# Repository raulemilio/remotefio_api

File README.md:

# BBRemoteIO - BeagleBone Black Remote I/O System

BBRemoteIO es un sistema de adquisición y control remoto basado en BeagleBone Black, diseñado para gestionar entradas y salidas de hardware a través de mensajes MQTT. Este módulo electrónico permite la integración con sensores, actuadores y otros dispositivos mediante la lectura de ADC, control de GPIOs y manejo de motores. Además, soporta la ejecución en paralelo de múltiples tareas y la integración con la PRU para adquisición de datos de alta velocidad. Ideal para aplicaciones en automatización, monitoreo remoto y laboratorios de instrumentación.

## Overview

BBRemoteIO is a remote I/O system for the BeagleBone Black, designed to execute tasks based on MQTT messages. The system can handle multiple tasks in parallel, including ADC data acquisition, GPIO input/output control, motor control, and interaction with an LCD display.

## Features

- **ADC Sampling**: Supports continuous sampling and triggered sampling.
- **GPIO Input/Output**: Reads input states and sets output states.
- **Motor Control**: Enables setting and querying motor states.
- **PRU Integration**: Uses the PRU for high-speed ADC data acquisition.
- **LCD Display**: Future module for logging and status display.
- **Parallel Execution**: Designed to handle multiple MQTT tasks without blocking.

## PRU (Cap15.pagina 667 libro BB)

### The PRU Code Generation Tools:

Download the PRU development framework from:
[PRU-CGT Tool](https://www.ti.com/tool/download/PRU-CGT)

Follow the project construction methodology as per the template: [Template Link](https://old.beagleboard.org/static/librobotcontrol/project_template.html)

## Compiling and Running ONLY PRU0

2. Configure GPIO pins:
   ```bash
   config-pin P8_16 pruin
   ```
   For more configuration options:
   ```bash
   config-pin -l P9_11
   ```
   To see the current configuration:
   ```bash
   config-pin -q P9_11
   ```

3. To export the pin and configure it:
```bash
echo "30" > /sys/class/gpio/export
echo "out" > /sys/class/gpio/gpio30/direction
echo "1" > /sys/class/gpio/gpio30/value  # Set high
echo "0" > /sys/class/gpio/gpio30/value  # Set low
```

4. Compile and load PRU firmware.

5. Check PRU state:
```bash
$ echo 'start' > /sys/class/remoteproc/remoteproc1/state
$ echo 'stop' > /sys/class/remoteproc/remoteproc1/state
```

### View PRU Registers:
```bash
$ sudo cat /sys/kernel/debug/remoteproc/remoteproc1/regs
```

### Test MQTT locally:

In one terminal:
```bash
$ mosquitto_sub -h localhost -t "test/topic"
```

In another terminal:
```bash
$ mosquitto_pub -h localhost -t "test/topic" -m "¡Hola desde BeagleBone!"
```

### Test MQTT between BeagleBone and Server:

1. Ping the server:
```bash
$ ping 192.168.0.171
```

2. On the notebook, open MQTT Explorer and connect to `tcp://192.168.0.171:1883`.
3. Subscribe to `test/topic` and send a message.

### Test MQTT Project:

Run the test MQTT project:
```bash
$ ./test_mqtt
```

## ADC Circuit

Based on:
- Book: "Analog Engineer's Circuit" (2023) Pg. 163
- Book: "Analog Engineer's Circuit" (2024) Pg. 160
- BeagleBook-Tool Pg. 443 (445 has protection for ADC inputs)
- Pg. 290 GIO

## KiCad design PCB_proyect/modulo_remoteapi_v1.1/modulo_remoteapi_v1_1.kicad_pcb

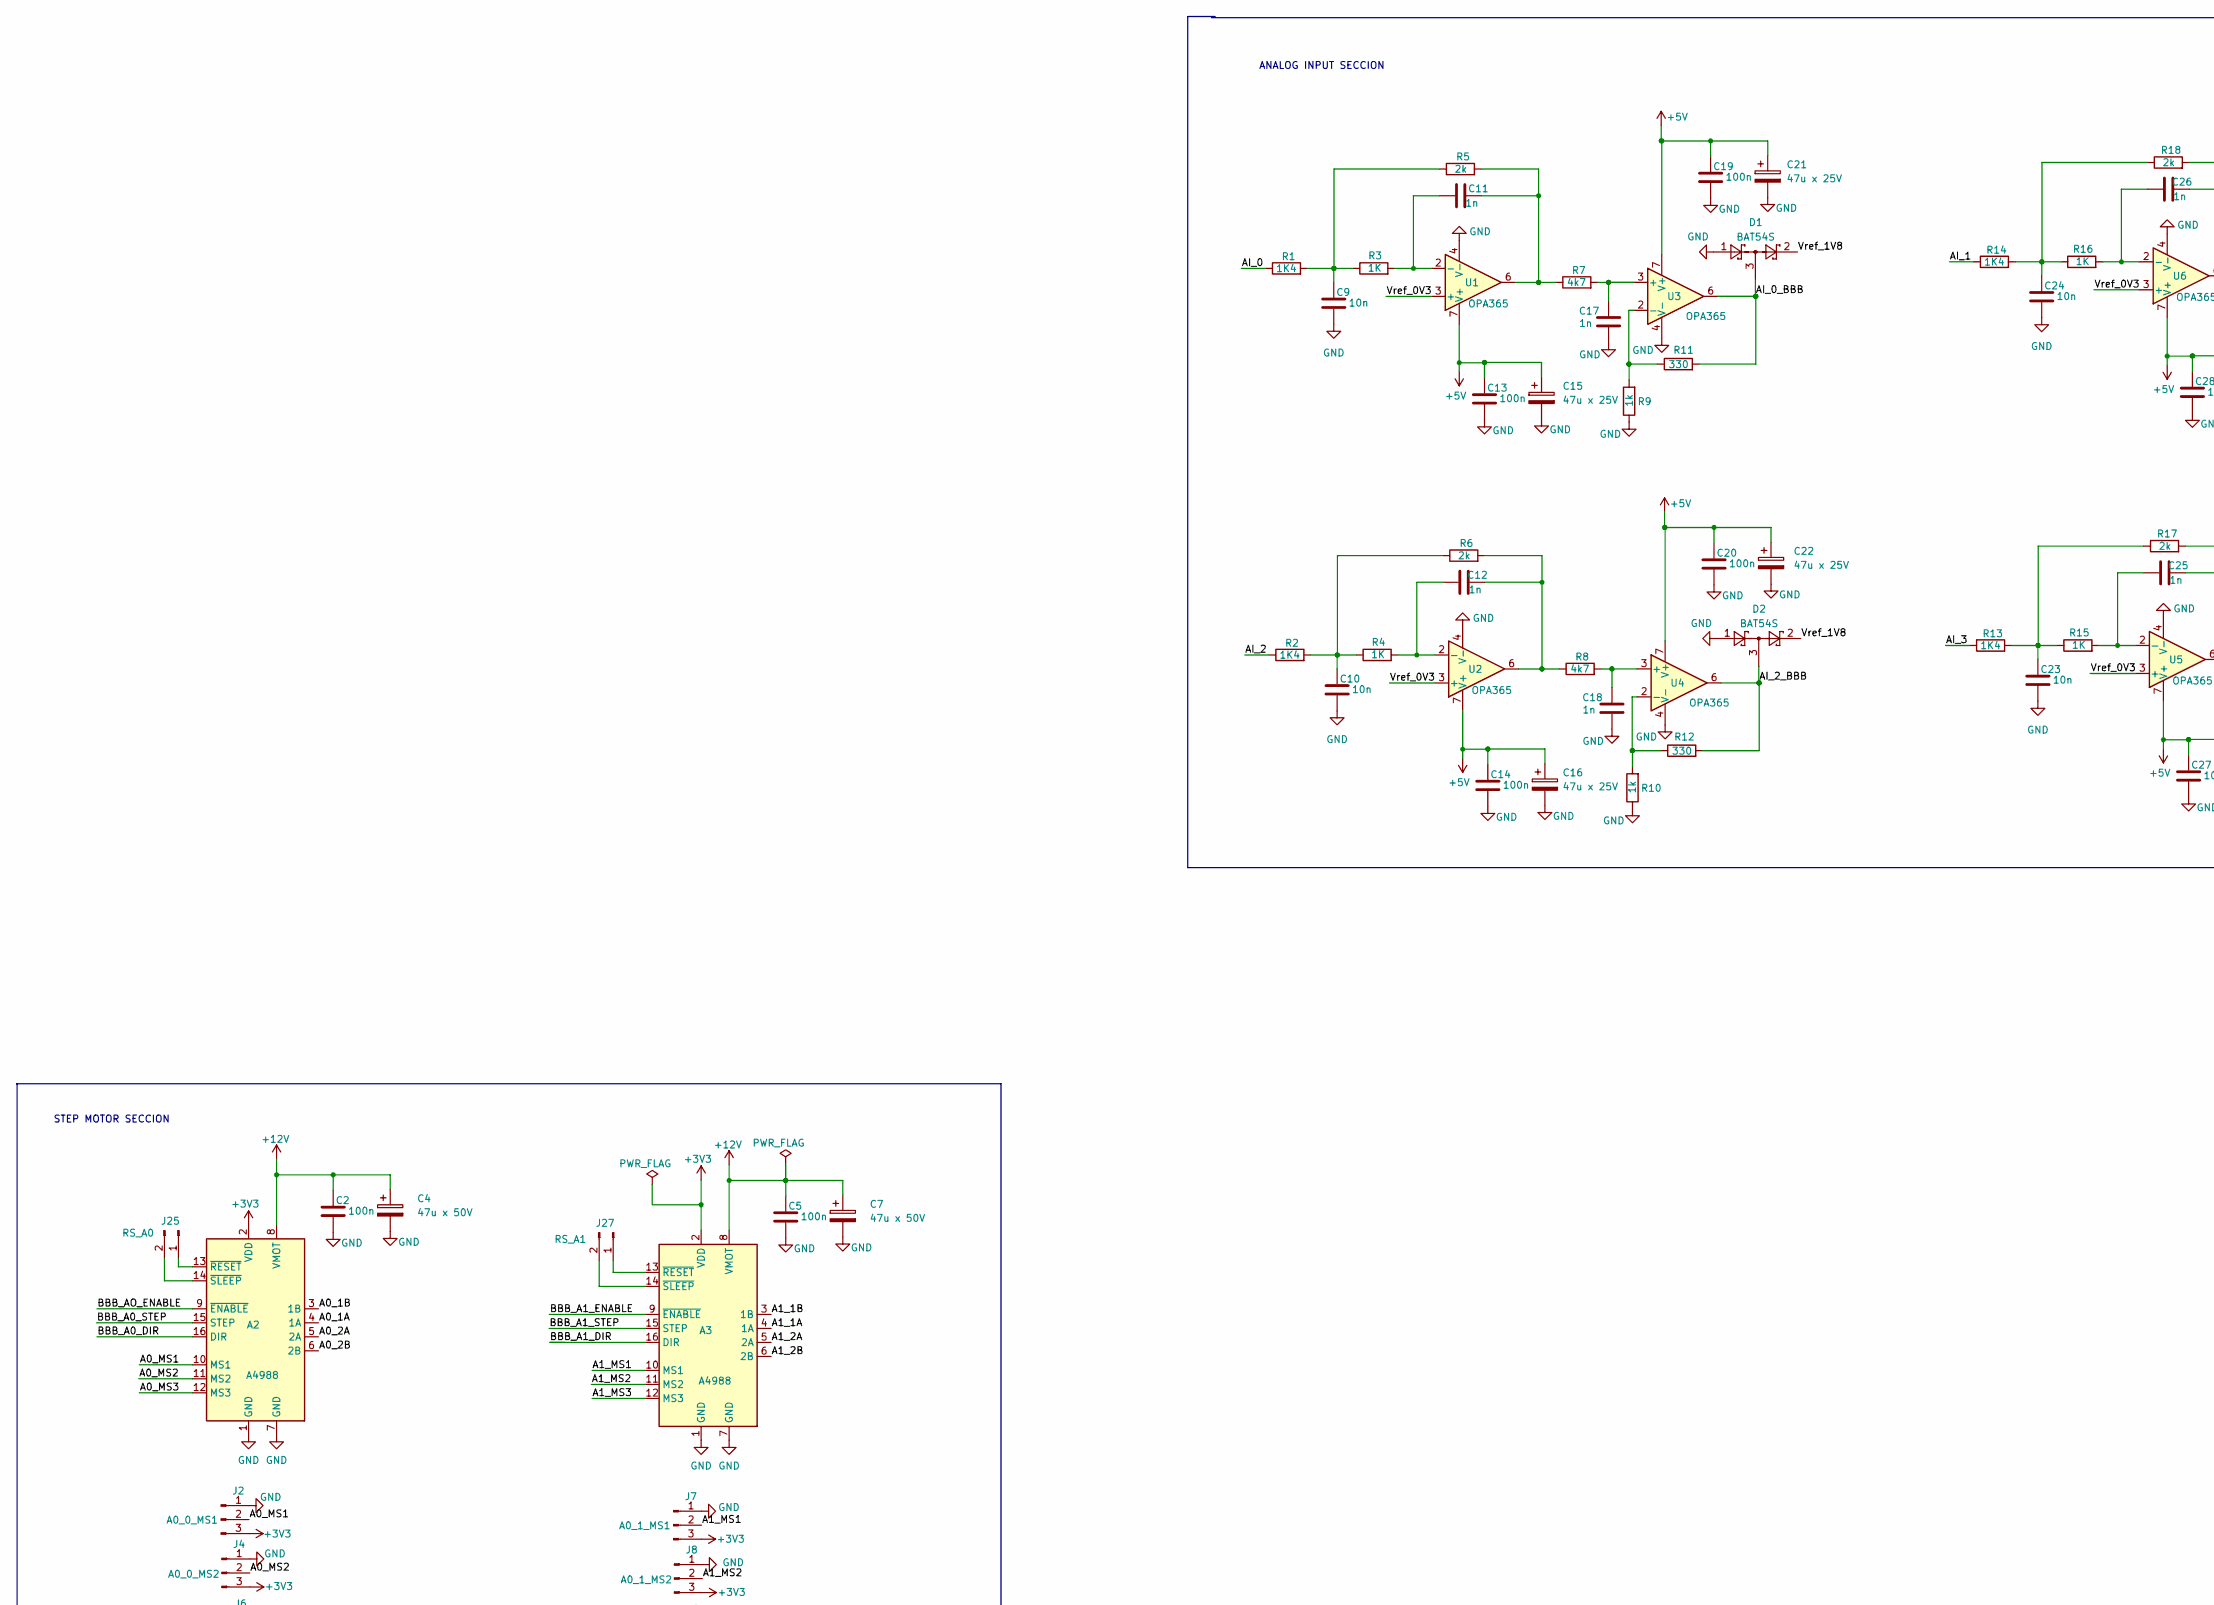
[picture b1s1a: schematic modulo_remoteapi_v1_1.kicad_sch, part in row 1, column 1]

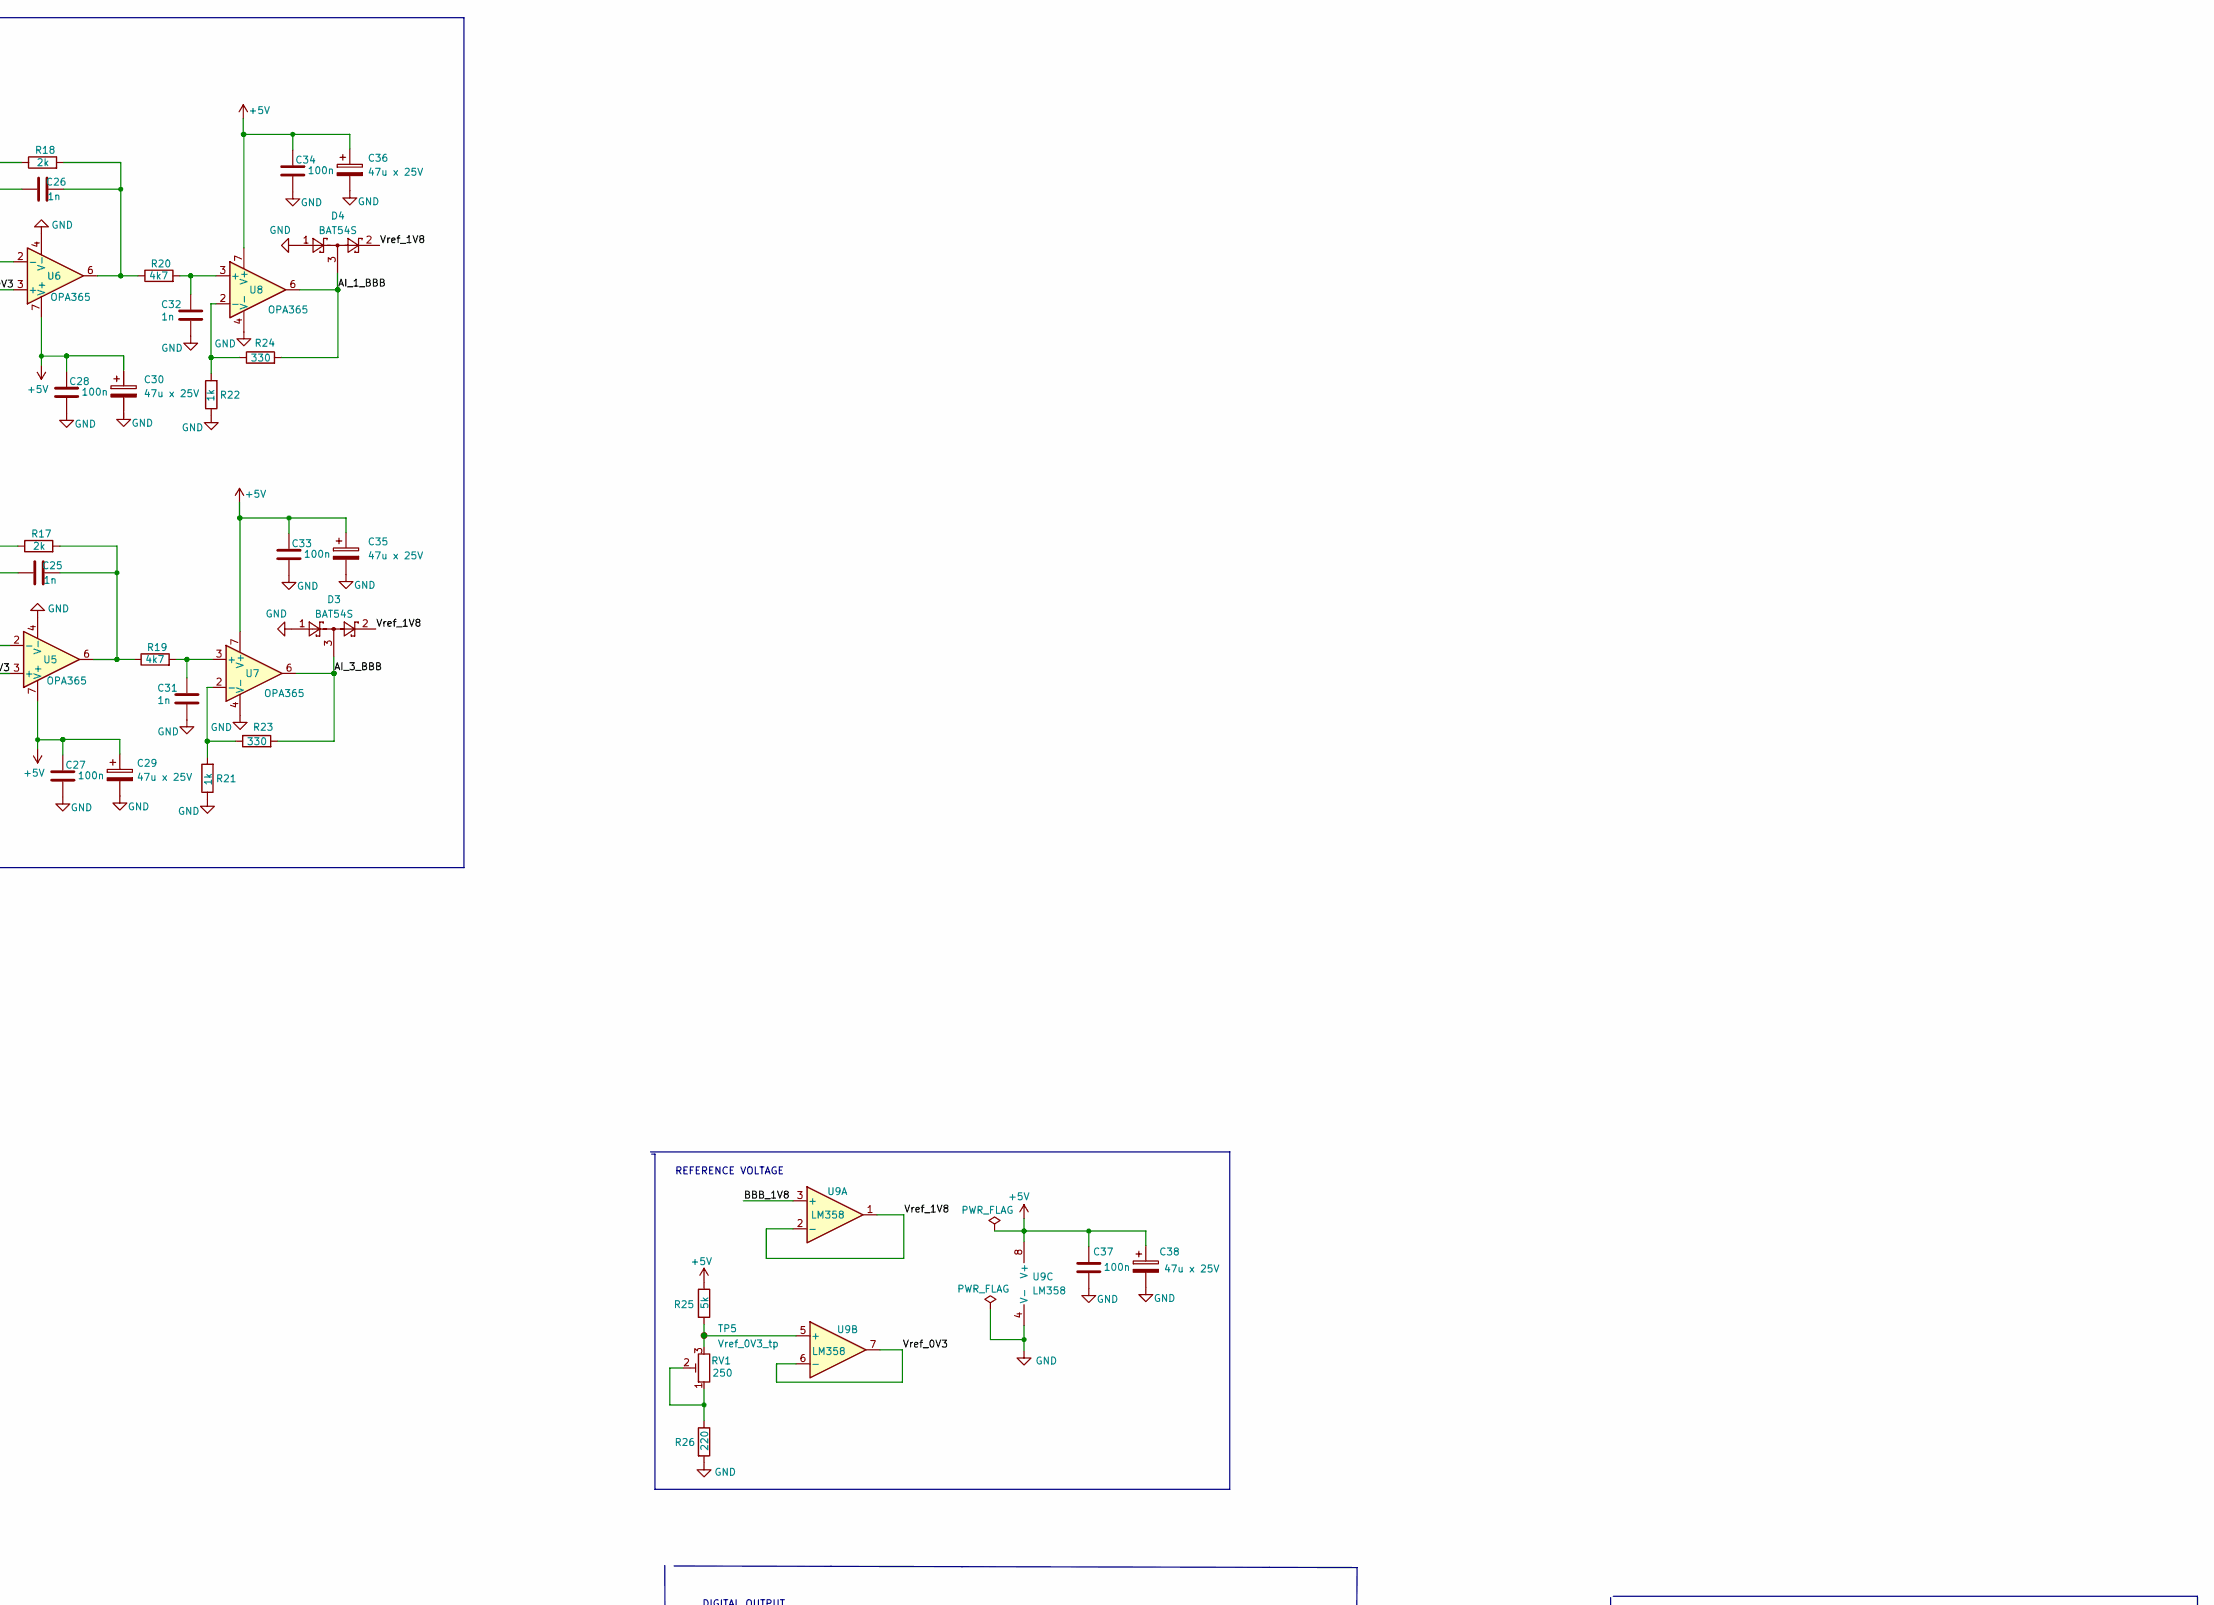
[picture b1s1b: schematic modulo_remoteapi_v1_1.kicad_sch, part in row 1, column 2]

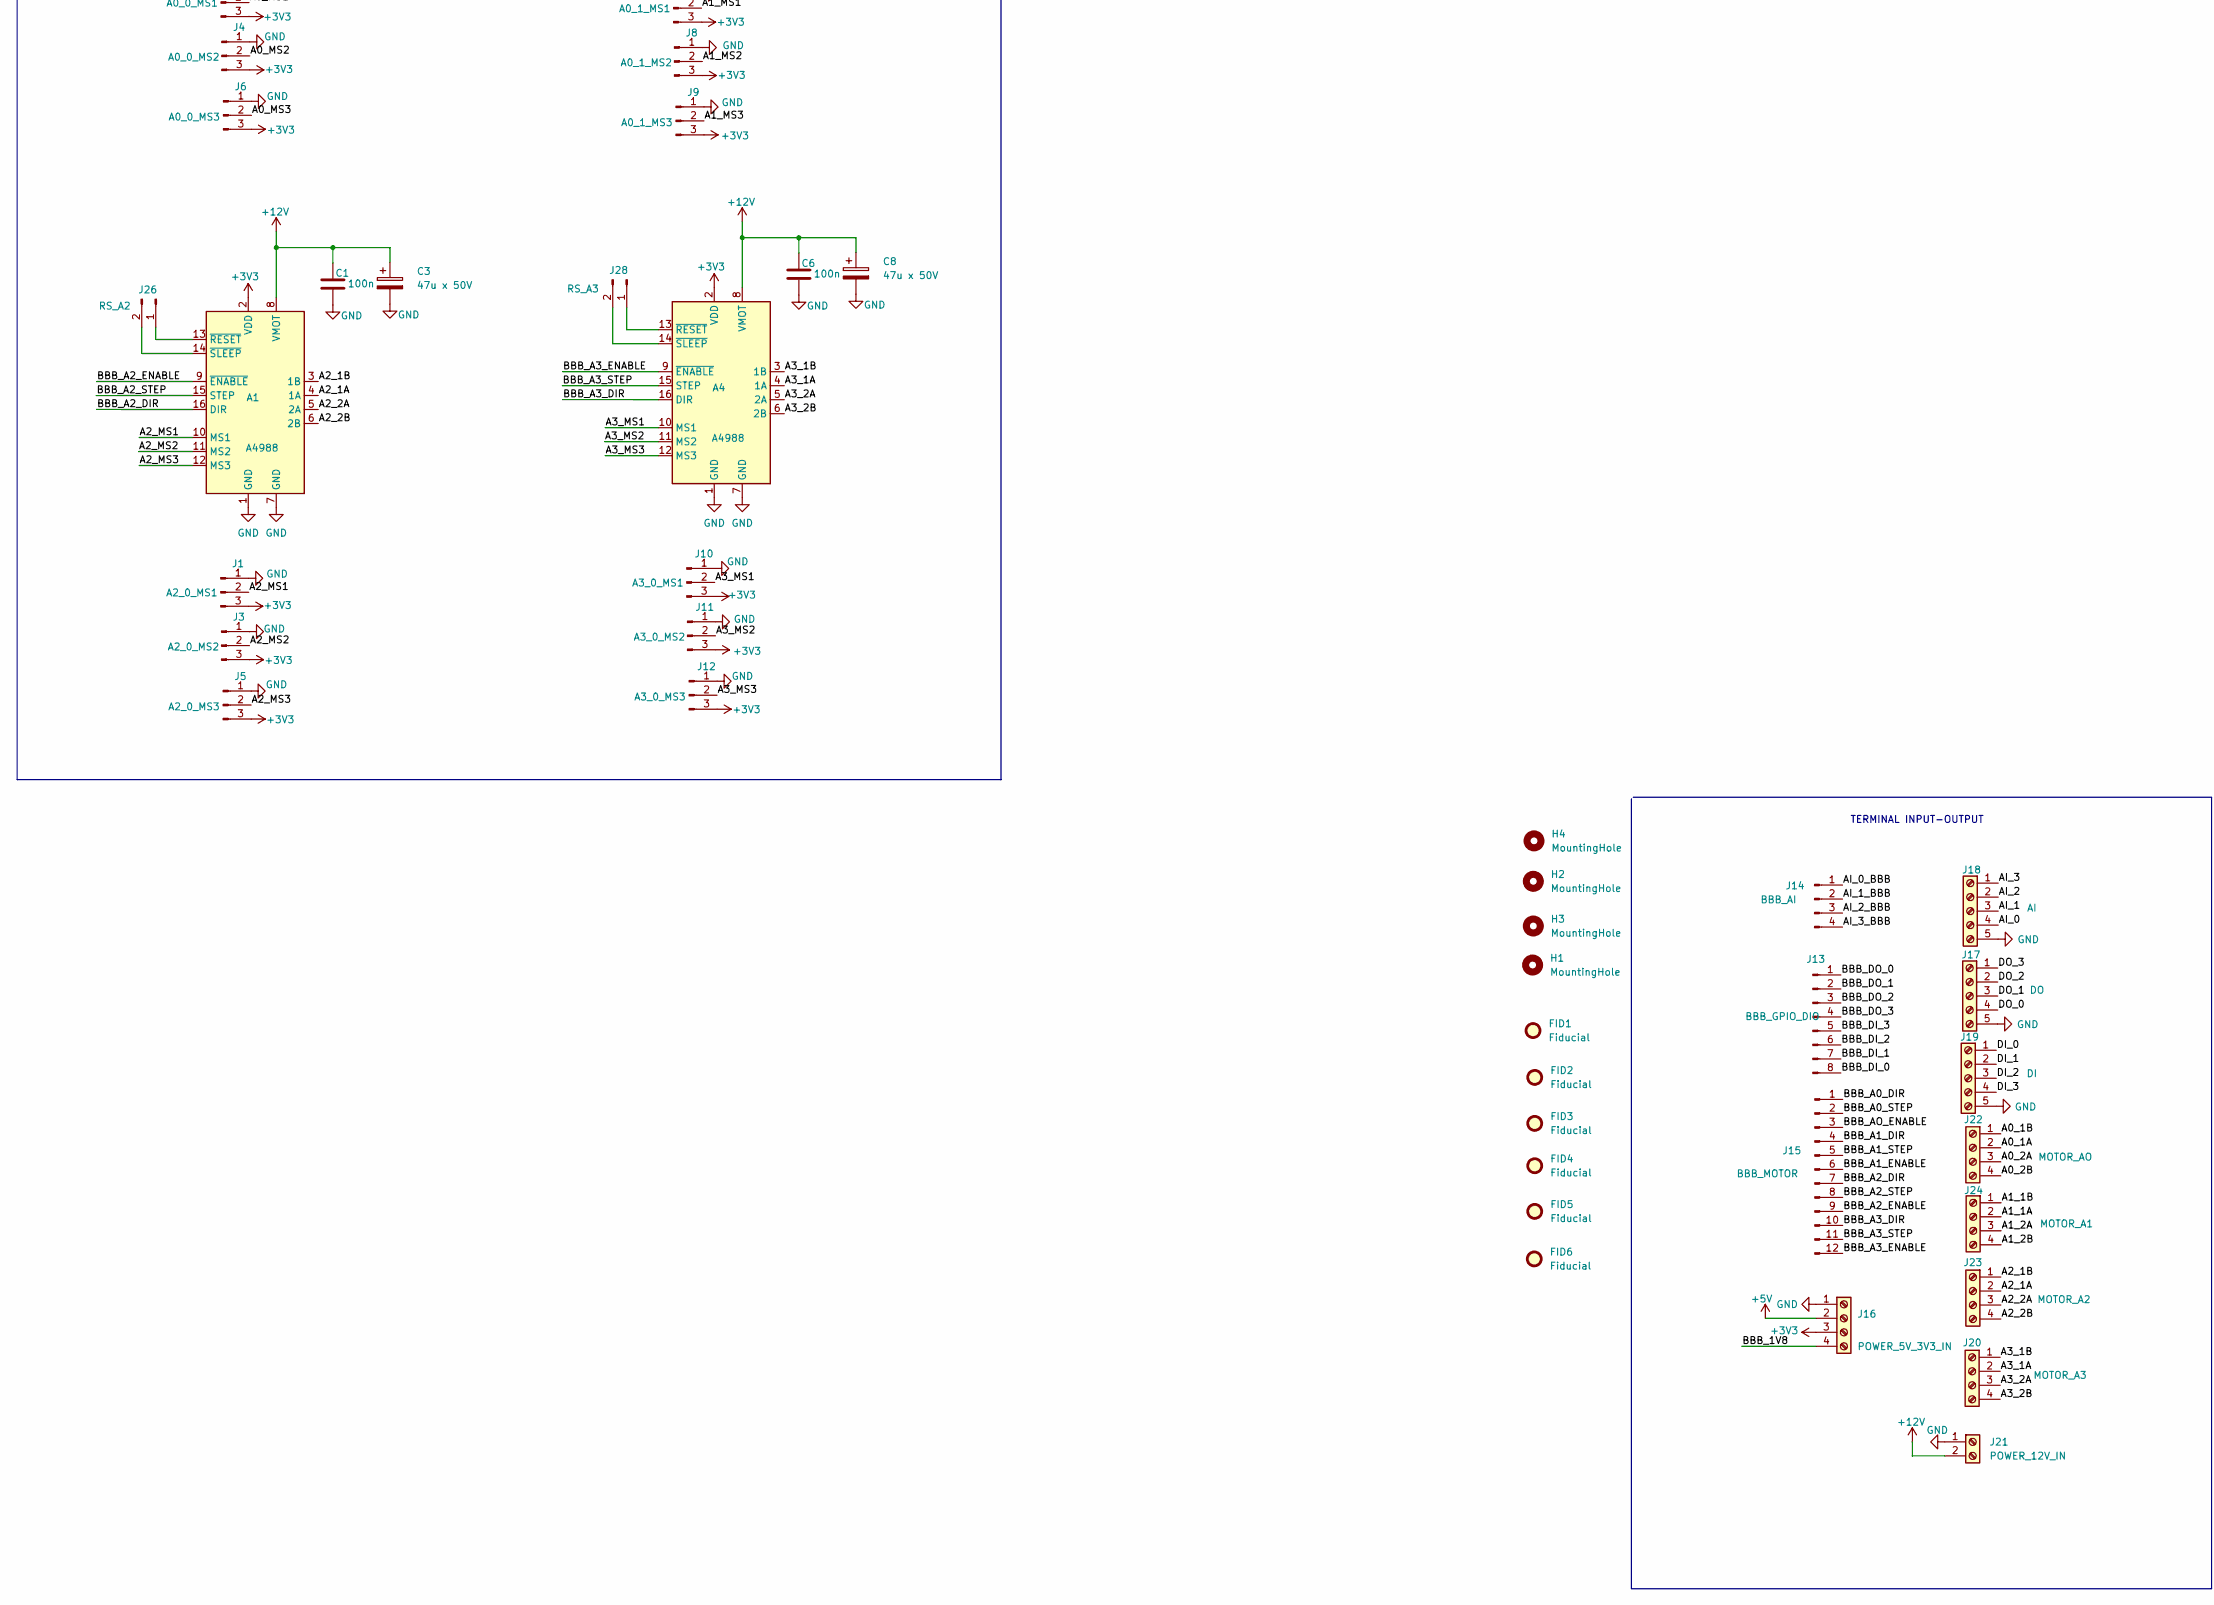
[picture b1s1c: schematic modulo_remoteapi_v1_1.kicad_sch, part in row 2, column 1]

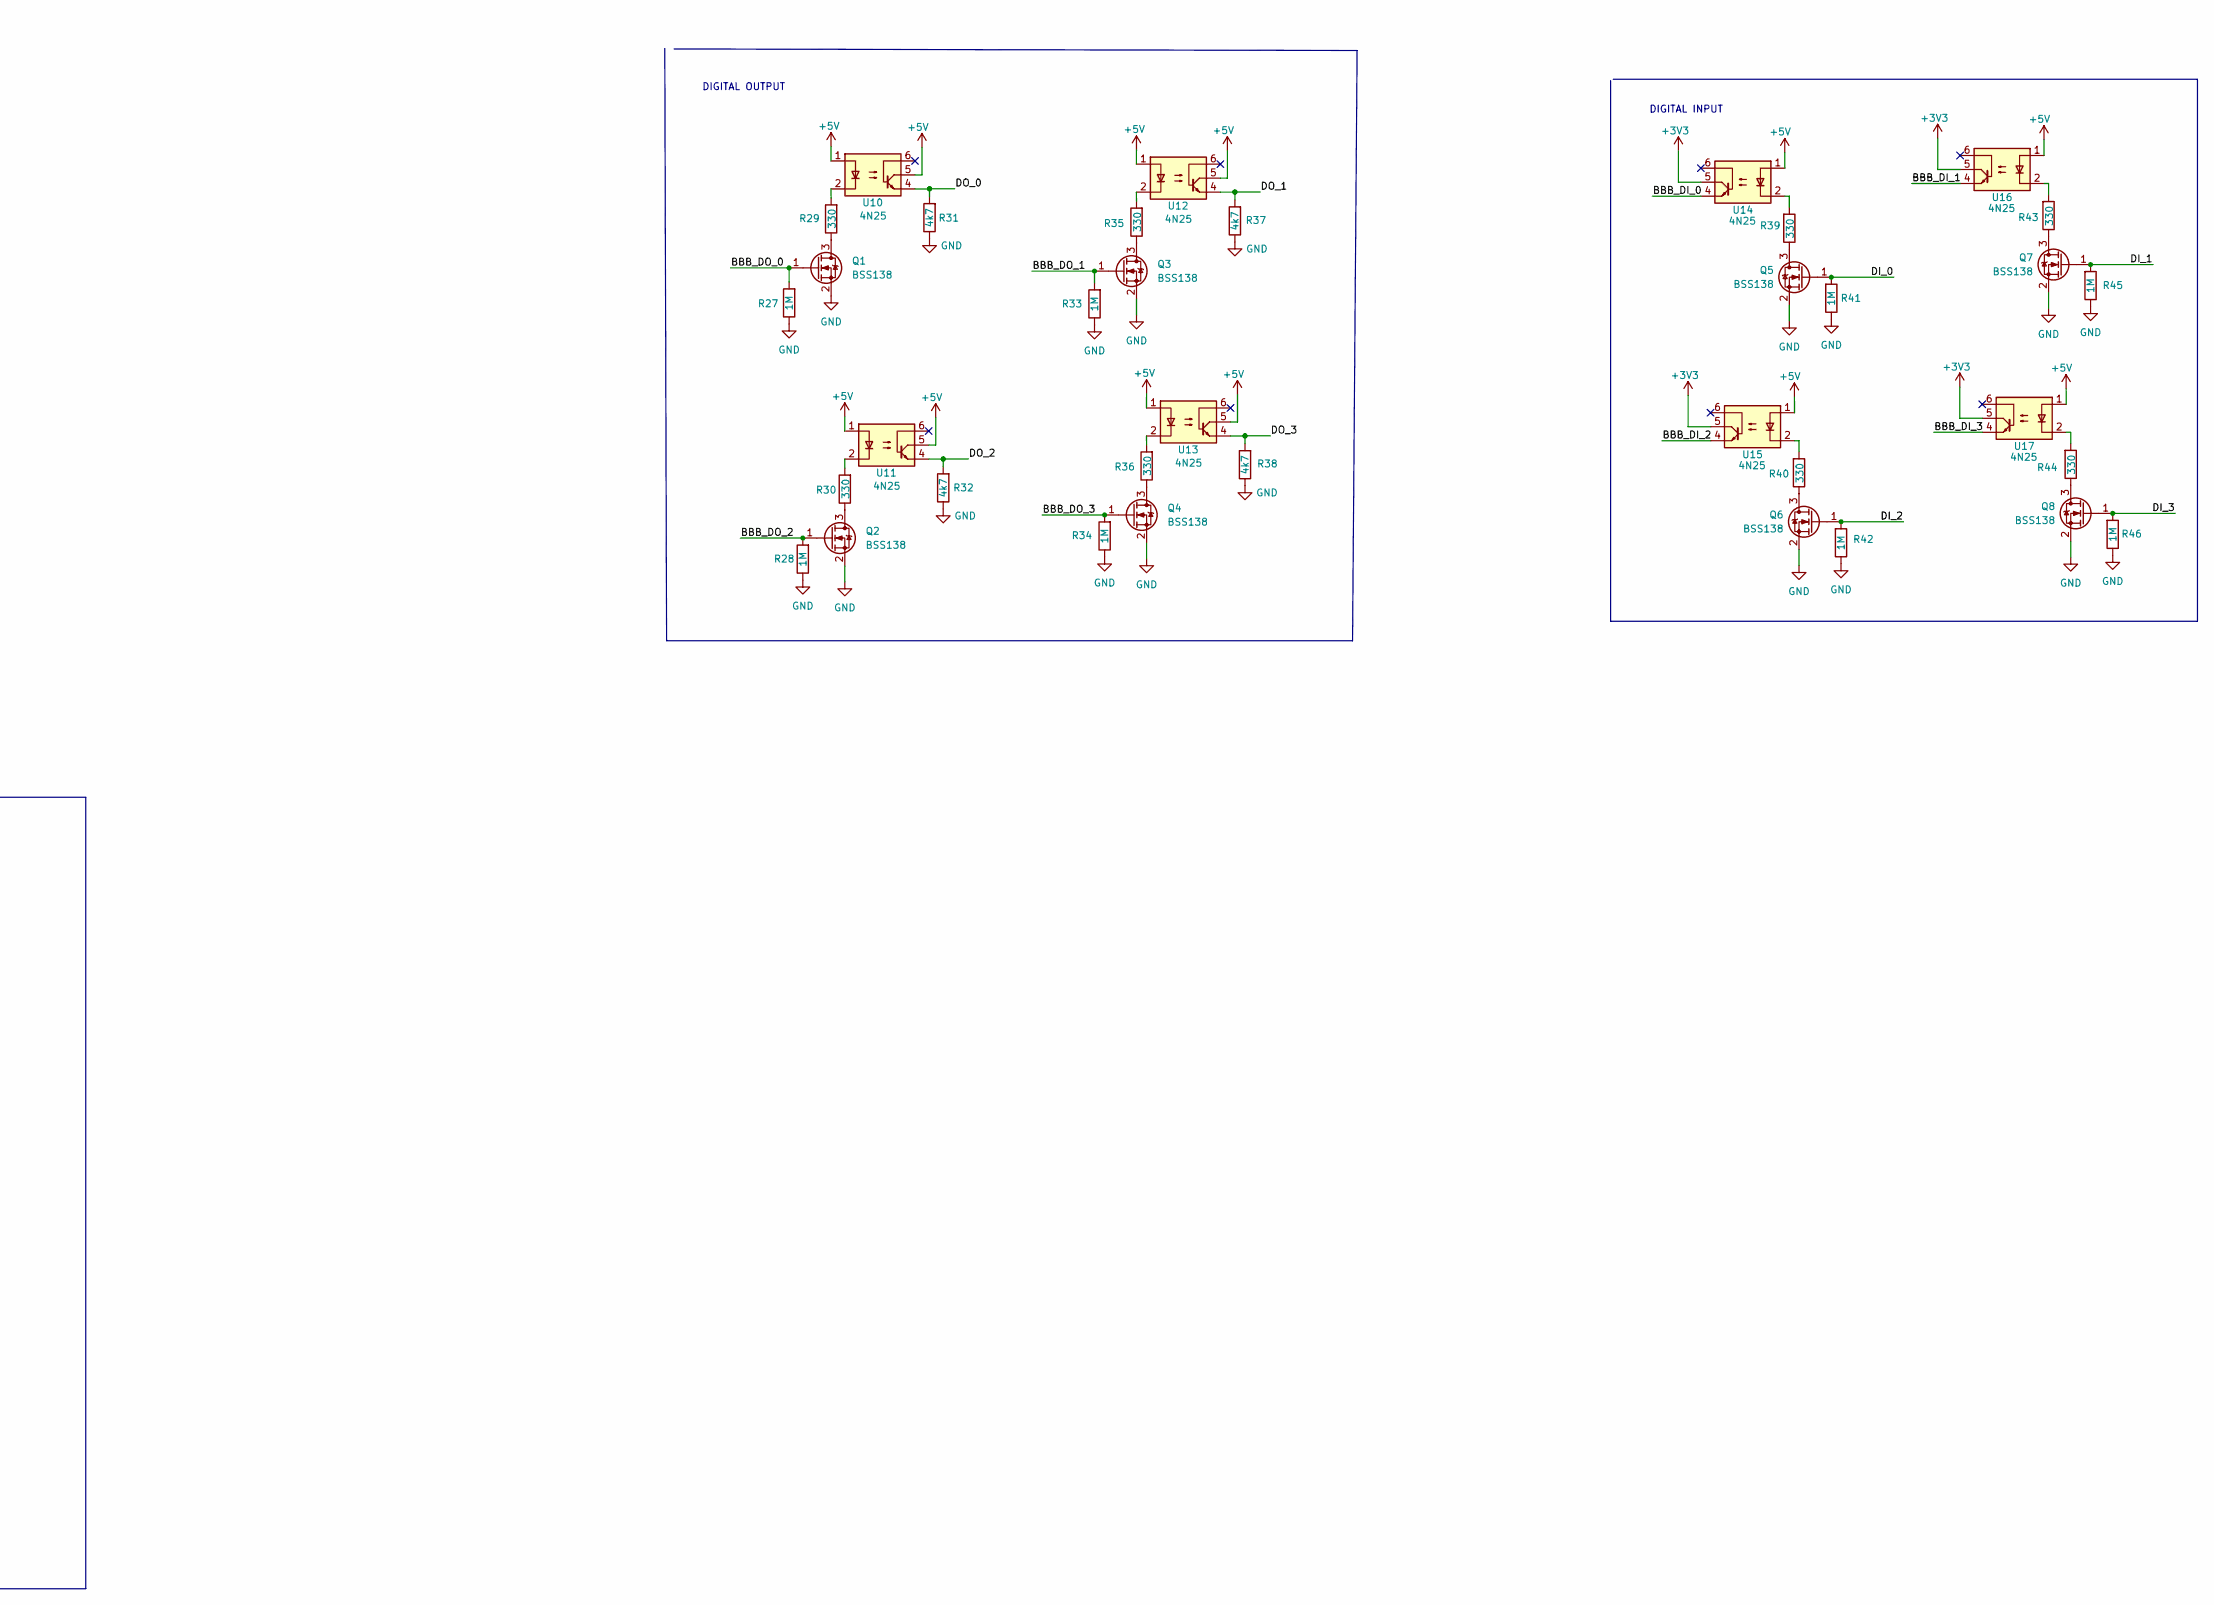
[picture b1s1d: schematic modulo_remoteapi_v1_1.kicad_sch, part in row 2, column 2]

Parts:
A1, A2, A3, A4: A4988; Pololu_Breakout-16_15.2x20.3mm
C1, C2, C5, C6: 100n; C_Disc_D3.0mm_W1.6mm_P2.50mm
C3, C4, C7, C8: 47u x 50V; CP_Radial_D8.0mm_P5.00mm
C9, C10, C23, C24: 10n; C_0805_2012Metric
C11, C12, C17, C18, C25, C26, C31, C32: 1n; C_0805_2012Metric
C13, C14, C19, C20, C27, C28, C33, C34, C37: 100n; C_0805_2012Metric
C15, C16, C21, C22, C29, C30, C35, C36, C38: 47u x 25V; CP_Radial_D6.3mm_P2.50mm
D1, D2, D3, D4: BAT54S; SOT-23
FID1, FID2, FID3, FID4, FID5, FID6: Fiducial; Fiducial_1mm_Mask2mm
H1, H2, H3, H4: MountingHole; MountingHole_3.5mm_Pad
J1: A2_0_MS1; PinHeader_1x03_P2.54mm_Vertical
J2: A0_0_MS1; PinHeader_1x03_P2.54mm_Vertical
J3: A2_0_MS2; PinHeader_1x03_P2.54mm_Vertical
J4: A0_0_MS2; PinHeader_1x03_P2.54mm_Vertical
J5: A2_0_MS3; PinHeader_1x03_P2.54mm_Vertical
J6: A0_0_MS3; PinHeader_1x03_P2.54mm_Vertical
J7: A0_1_MS1; PinHeader_1x03_P2.54mm_Vertical
J8: A0_1_MS2; PinHeader_1x03_P2.54mm_Vertical
J9: A0_1_MS3; PinHeader_1x03_P2.54mm_Vertical
J10: A3_0_MS1; PinHeader_1x03_P2.54mm_Vertical
J11: A3_0_MS2; PinHeader_1x03_P2.54mm_Vertical
J12: A3_0_MS3; PinHeader_1x03_P2.54mm_Vertical
J13: BBB_GPIO_DIO; PinHeader_1x08_P2.54mm_Vertical
J14: BBB_AI; PinHeader_1x04_P2.54mm_Vertical
J15: BBB_MOTOR; PinHeader_1x12_P2.54mm_Vertical
J16: POWER_5V_3V3_IN; TerminalBlock_bornier-4_P5.08mm
J17: DO; TerminalBlock_bornier-5_P5.08mm
J18: AI; TerminalBlock_bornier-5_P5.08mm
J19: DI; TerminalBlock_bornier-5_P5.08mm
J20: MOTOR_A3; TerminalBlock_bornier-4_P5.08mm
J21: POWER_12V_IN; TerminalBlock_bornier-2_P5.08mm
J22: MOTOR_AO; TerminalBlock_bornier-4_P5.08mm
J23: MOTOR_A2; TerminalBlock_bornier-4_P5.08mm
J24: MOTOR_A1; TerminalBlock_bornier-4_P5.08mm
J25: RS_A0; PinHeader_1x02_P2.54mm_Vertical
J26: RS_A2; PinHeader_1x02_P2.54mm_Vertical
J27: RS_A1; PinHeader_1x02_P2.54mm_Vertical
J28: RS_A3; PinHeader_1x02_P2.54mm_Vertical
Q1, Q2, Q3, Q4, Q5, Q6, Q7, Q8: BSS138; SOT-23
R1, R2, R13, R14: 1K4; R_1206_3216Metric
R3, R4, R15, R16: 1K; R_1206_3216Metric
R5, R6, R17, R18: 2k; R_1206_3216Metric
R7, R8, R19, R20, R31, R32, R37, R38: 4k7; R_1206_3216Metric
R9, R10, R21, R22: 1k; R_1206_3216Metric
R11, R12, R23, R24, R29, R30, R35, R36, R39, R40, R43, R44: 330; R_1206_3216Metric
R25: 5k; R_1206_3216Metric
R26: 220; R_1206_3216Metric
R27, R28, R33, R34, R41, R42, R45, R46: 1M; R_1206_3216Metric
RV1: 250; Potentiometer_Bourns_3296W_Vertical
TP5: Vref_0V3_tp; TestPoint_Pad_D1.5mm
U1, U2, U3, U4, U5, U6, U7, U8: OPA365; SOIC-8_3.9x4.9mm_P1.27mm
U9: LM358; SOIC-8_3.9x4.9mm_P1.27mm
U10, U11, U12, U13, U14, U15, U16, U17: 4N25; DIP-6_W7.62mm

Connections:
+3V3: A1.2 (VDD), A2.2 (VDD), A3.2 (VDD), A4.2 (VDD), J1.3, J2.3, J3.3, J4.3, J5.3, J6.3, J7.3, J8.3, J9.3, J10.3, J11.3, J12.3, J16.3, U14.5, U15.5, U16.5, U17.5
+5V: C13.1, C14.1, C15.1, C16.1, C19.1, C20.1, C21.1, C22.1, C27.1, C28.1, C29.1, C30.1, C33.1, C34.1, C35.1, C36.1, C37.1, C38.1, J16.2, R25.1, U1.7 (V+), U2.7 (V+), U3.7 (V+), U4.7 (V+), U5.7 (V+), U6.7 (V+), U7.7 (V+), U8.7 (V+), U9.8 (V+), U10.1, U10.5, U11.1, U11.5, U12.1, U12.5, U13.1, U13.5, U14.1, U15.1, U16.1, U17.1
+12V: A1.8 (VMOT), A2.8 (VMOT), A3.8 (VMOT), A4.8 (VMOT), C1.1, C2.1, C3.1, C4.1, C5.1, C6.1, C7.1, C8.1, J21.2
/A0_1A: A2.4 (1A), J22.2
/A0_1B: A2.3 (1B), J22.1
/A0_2A: A2.5 (2A), J22.3
/A0_2B: A2.6 (2B), J22.4
/A0_MS1: A2.10 (MS1), J2.2
/A0_MS2: A2.11 (MS2), J4.2
/A0_MS3: A2.12 (MS3), J6.2
/A1_1A: A3.4 (1A), J24.2
/A1_1B: A3.3 (1B), J24.1
/A1_2A: A3.5 (2A), J24.3
/A1_2B: A3.6 (2B), J24.4
/A1_MS1: A3.10 (MS1), J7.2
/A1_MS2: A3.11 (MS2), J8.2
/A1_MS3: A3.12 (MS3), J9.2
/A2_1A: A1.4 (1A), J23.2
/A2_1B: A1.3 (1B), J23.1
/A2_2A: A1.5 (2A), J23.3
/A2_2B: A1.6 (2B), J23.4
/A2_MS1: A1.10 (MS1), J1.2
/A2_MS2: A1.11 (MS2), J3.2
/A2_MS3: A1.12 (MS3), J5.2
/A3_1A: A4.4 (1A), J20.2
/A3_1B: A4.3 (1B), J20.1
/A3_2A: A4.5 (2A), J20.3
/A3_2B: A4.6 (2B), J20.4
/A3_MS1: A4.10 (MS1), J10.2
/A3_MS2: A4.11 (MS2), J11.2
/A3_MS3: A4.12 (MS3), J12.2
/AI_0: J18.4, R1.1
/AI_0_BBB: D1.3, J14.1, R11.2, U3.6
/AI_1: J18.3, R14.1
/AI_1_BBB: D4.3, J14.2, R24.2, U8.6
/AI_2: J18.2, R2.1
/AI_2_BBB: D2.3, J14.3, R12.2, U4.6
/AI_3: J18.1, R13.1
/AI_3_BBB: D3.3, J14.4, R23.2, U7.6
/BBB_1V8: J16.4, U9.3 (+)
/BBB_A0_DIR: A2.16 (DIR), J15.1
/BBB_A0_STEP: A2.15 (STEP), J15.2
/BBB_A1_DIR: A3.16 (DIR), J15.4
/BBB_A1_ENABLE: A3.9 (~ENABLE), J15.6
/BBB_A1_STEP: A3.15 (STEP), J15.5
/BBB_A2_DIR: A1.16 (DIR), J15.7
/BBB_A2_ENABLE: A1.9 (~ENABLE), J15.9
/BBB_A2_STEP: A1.15 (STEP), J15.8
/BBB_A3_DIR: A4.16 (DIR), J15.10
/BBB_A3_ENABLE: A4.9 (~ENABLE), J15.12
/BBB_A3_STEP: A4.15 (STEP), J15.11
/BBB_AO_ENABLE: A2.9 (~ENABLE), J15.3
/BBB_DI_0: J13.8, U14.4
/BBB_DI_1: J13.7, U16.4
/BBB_DI_2: J13.6, U15.4
/BBB_DI_3: J13.5, U17.4
/BBB_DO_0: J13.1, Q1.1 (G), R27.2
/BBB_DO_1: J13.2, Q3.1 (G), R33.2
/BBB_DO_2: J13.3, Q2.1 (G), R28.2
/BBB_DO_3: J13.4, Q4.1 (G), R34.2
/DI_0: J19.1, Q5.1 (G), R41.2
/DI_1: J19.2, Q7.1 (G), R45.2
/DI_2: J19.3, Q6.1 (G), R42.2
/DI_3: J19.4, Q8.1 (G), R46.2
/DO_0: J17.4, R31.2, U10.4
/DO_1: J17.3, R37.2, U12.4
/DO_2: J17.2, R32.2, U11.4
/DO_3: J17.1, R38.2, U13.4
/Vref_0V3: U1.3 (+), U2.3 (+), U5.3 (+), U6.3 (+), U9.6 (-), U9.7
/Vref_1V8: D1.2, D2.2, D3.2, D4.2, U9.1, U9.2 (-)
GND: A1.1 (GND), A1.7 (GND), A2.1 (GND), A2.7 (GND), A3.1 (GND), A3.7 (GND), A4.1 (GND), A4.7 (GND), C1.2, C2.2, C3.2, C4.2, C5.2, C6.2, C7.2, C8.2, C9.2, C10.2, C13.2, C14.2, C15.2, C16.2, C17.2, C18.2, C19.2, C20.2, C21.2, C22.2, C23.2, C24.2, C27.2, C28.2, C29.2, C30.2, C31.2, C32.2, C33.2, C34.2, C35.2, C36.2, C37.2, C38.2, D1.1, D2.1, D3.1, D4.1, J1.1, J2.1, J3.1, J4.1, J5.1, J6.1, J7.1, J8.1, J9.1, J10.1, J11.1, J12.1, J16.1, J17.5, J18.5, J19.5, J21.1, Q1.2 (S), Q2.2 (S), Q3.2 (S), Q4.2 (S), Q5.2 (S), Q6.2 (S), Q7.2 (S), Q8.2 (S), R9.1, R10.1, R21.1, R22.1, R26.2, R27.1, R28.1, R31.1, R32.1, R33.1, R34.1, R37.1, R38.1, R41.1, R42.1, R45.1, R46.1, U1.4 (V-), U2.4 (V-), U3.4 (V-), U4.4 (V-), U5.4 (V-), U6.4 (V-), U7.4 (V-), U8.4 (V-), U9.4 (V-)
unnamed: A1.13 (~RESET), J26.1
unnamed: A1.14 (~SLEEP), J26.2
unnamed: A2.13 (~RESET), J25.1
unnamed: A2.14 (~SLEEP), J25.2
unnamed: A3.13 (~RESET), J27.1
unnamed: A3.14 (~SLEEP), J27.2
unnamed: A4.13 (~RESET), J28.1
unnamed: A4.14 (~SLEEP), J28.2
unnamed: C9.1, R1.2, R3.1, R5.1
unnamed: C10.1, R2.2, R4.1, R6.1
unnamed: C11.1, R3.2, U1.2 (-)
unnamed: C11.2, R5.2, R7.1, U1.6
unnamed: C12.1, R4.2, U2.2 (-)
unnamed: C12.2, R6.2, R8.1, U2.6
unnamed: C17.1, R7.2, U3.3 (+)
unnamed: C18.1, R8.2, U4.3 (+)
unnamed: C23.1, R13.2, R15.1, R17.1
unnamed: C24.1, R14.2, R16.1, R18.1
unnamed: C25.1, R15.2, U5.2 (-)
unnamed: C25.2, R17.2, R19.1, U5.6
unnamed: C26.1, R16.2, U6.2 (-)
unnamed: C26.2, R18.2, R20.1, U6.6
unnamed: C31.1, R19.2, U7.3 (+)
unnamed: C32.1, R20.2, U8.3 (+)
unnamed: Q1.3 (D), R29.1
unnamed: Q2.3 (D), R30.1
unnamed: Q3.3 (D), R35.1
unnamed: Q4.3 (D), R36.1
unnamed: Q5.3 (D), R39.1
unnamed: Q6.3 (D), R40.1
unnamed: Q7.3 (D), R43.1
unnamed: Q8.3 (D), R44.1
unnamed: R10.2, R12.1, U4.2 (-)
unnamed: R9.2, R11.1, U3.2 (-)
unnamed: R21.2, R23.1, U7.2 (-)
unnamed: R22.2, R24.1, U8.2 (-)
unnamed: R25.2, RV1.3, TP5.1, U9.5 (+)
unnamed: R26.1, RV1.1, RV1.2
unnamed: R29.2, U10.2
unnamed: R30.2, U11.2
unnamed: R35.2, U12.2
unnamed: R36.2, U13.2
unnamed: R39.2, U14.2
unnamed: R40.2, U15.2
unnamed: R43.2, U16.2
unnamed: R44.2, U17.2

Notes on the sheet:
STEP MOTOR SECCION
DIGITAL OUTPUT
TERMINAL INPUT-OUTPUT
DIGITAL INPUT
REFERENCE VOLTAGE
ANALOG INPUT SECCION

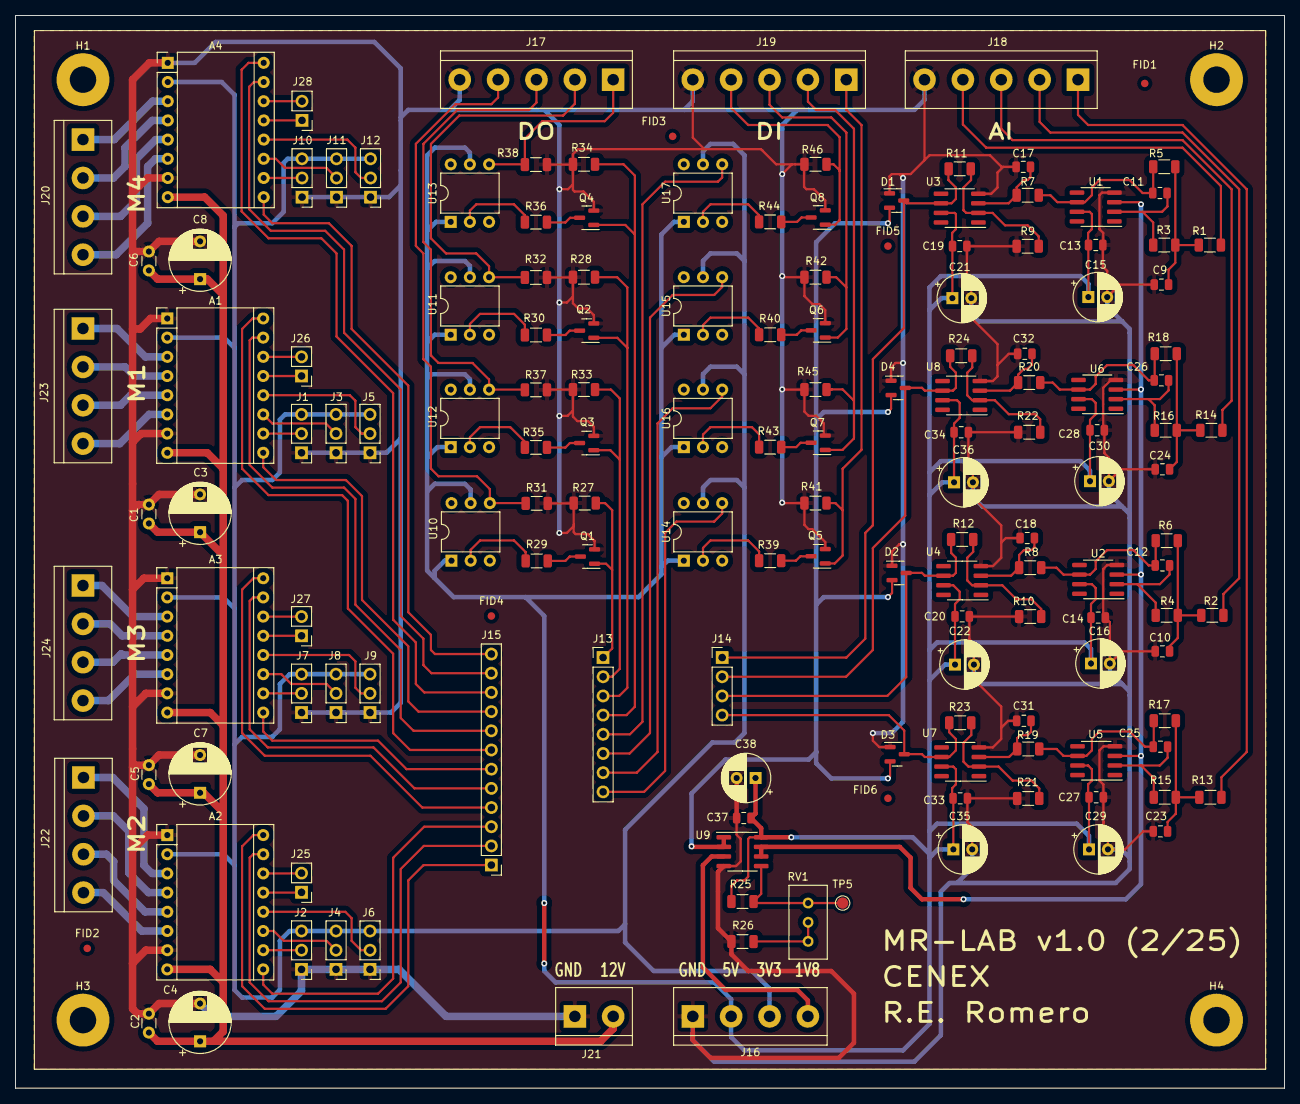
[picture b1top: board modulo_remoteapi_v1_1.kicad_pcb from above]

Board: 2 copper layers, 168.0 x 142.0 mm, 157 parts (0 on the bottom side), 117 nets.

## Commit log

2025-02-10 actu repo
2025-04-04 se modifico el redme
2025-04-09 se agrego documentacion
2025-04-19 release version
2025-04-27 nueva actualizacion gpio_input
2025-04-27 nueva actualizacion flow node-red
2025-04-28 nueva actualizacion flow node-red nueva version
2025-04-29 nueva actualizacion flow node-red y motor_get
2025-04-29 comandos mqtt
2025-04-30 comandos node list
2025-04-30 comandos node list msg
2025-05-01 configuracion de pines
2025-05-01 configuracion fuchas y readme
2025-05-01 correciones en readme
2025-05-03 version 1.0
2025-05-06 version final 1.0
2025-05-11 version 1-0 actualizada
2025-06-03 version pruebas finales
2025-06-03 pin adc gnd
